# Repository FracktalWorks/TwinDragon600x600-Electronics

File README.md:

# TwinDragon600x600-Electronics
Electronic description, pinout and manuals for the electronics used in Twin Dragon 600x600x600 (Enhanced Size)

### For the Combination of BTT Manta M8P V2.0 + RPi CM4 + RP2040 based toolboard

Pin Configurations, jumper selection, CanBus and multi-MCU wiring to RPi CM4 embedded onto BTT Manta M8P V2.0 for Twin Dragon 600x600x600

Components used:
1. BTT Manta M8P V2.0 - 1
2. RPi CM4 (embed onto BTT Manta M8P V2.0) - 1
3. RP2040 based Can Module/Toolboard - 2
4. TMC5160 Stepper drivers - 4
5. TMC5160T Plus Z driver - 1
6. TMC2209 stepper drivers - 2 (External) + 2 (Present on the Toolboards)
7. BTT HDMI5 Touch Display

## Setting up BTT Manta M8P V2.0 + RPi CM4 + RP2040 based toolboard

After powering on the M8P, the LED on the bottom left corner will light up to indicate normal power supply. The VUSB jumper in the center is for selecting power - it should only be shorted when powering the board via USB or supplying power out via USB.

### Other Initial preparation and setting up jumpers

#### TMC Driver SPI Mode

The first row are the defined pin for the drivers, which are either high or low when shorted or unshorted to establish different mode of communication. The second row are defined with the SPI modes, with the namings of 'MISO', 'CS', 'SCK' and 'MOSI' when read from left to right. Since we use the TMC5160 driver, it specifically operates only on the SPI mode. Insert the jumpers corresponding to its parallel pins only on the 1st and the 2nd row as shown in the image.

#### TMC Driver UART Mode

The given set of pin to short is the CS pin that enables only the uart mode.

#### Driver Voltage selection

For High Voltage selection(48V):

Since the TMC5160 operates only on SPI mode, which is specifically for achieving faster communication and higher speeds, it needs an operating voltage of around 48V. The manta M8P has seperte pins for regular voltage of 24V and high voltage of 48V, that is to be jumped to the common pin of voltage supply to the drivers. We jump the HV pin in the left to the middle pin of supply in order to provide 48V to the drivers, as shown in the image above.

For normal Voltage selection (24V):

This voltage selection can be used when using a regular TMC2209 on the UART mode

#### Setting up jumper for probe activation

The pin for probe used here is the IND-probe pin on Manta M8P V2.0, and the jumpers are placed on the two pins beside the probe pins, and other three perpendicular pins to its right, where the top two are to jumped together to activate the probe pin, as shown in the image above, to enable 24V/5V supply to the ABL board. The three columns of the pins starting from the top are 5V, 12V, 24V Respectively.

#### Setting up Jumper for CANBUS communication

At the left of the CAN pin, a small jumper is to be placed on the pins that mention '120R' depicting the 120 ohms resistance that is applied on the CAN Low and High communication pins. This is a crucial pin for the setting up of the CAN communication of the motherboard and toolboard.

## Wiring and Connections

The overall connections of all the Electrical and Electronic components are present in the image above

### BTT Manta M8P V2.0 Pin connections

## Dragon ToolBoard Pinout Mappings

## Guide to place the connectors on the Carriage Minifit Board

## To setup Raspeberry Pi camera Rev 1.3, interfaced with RPi CM4 and BTT Manta M8P/M5P

In order to interface the Pi camera Rev 1.3 with the RPi CM4 and BTT Manta M8P/M5P, flip the board and check for a CSI1 camera slot, which should look like the image below

Instructions to attach the camera in BTT Manta M8P V2.0

Instructions to attach the camera in BTT Manta M8P V2.0

1. Now, boot up the board (including CM4), SSH into the CM4 and open the terminal
2. We will have to download a bin file into the boot folder of the CM4, below is the command to enter into the terminal.

`sudo wget https://datasheets.raspberrypi.com/cmio/dt-blob-cam1.bin -O /boot/dt-blob.bin`

If the above command does not work, try the following command:

`sudo wget https://datasheets.raspberrypi.com/cmio/dt-blob-cam1.bin -O /boot/firmware/dt-blob.bin`

3. Now, in the terminal, enter `sudo raspi-config` and select the option '3 Interface Options    Configure connections to peripherals'. Now select the first option 'P1 Camera      Enable/disable connection to the Raspberry Pi Camera'. A pop-up would appear where it asks to enable the camera. Make sure to select <yes> and exit the portal.

4. Now, in the terminal, type in `sudo nano /boot/config.txt` and make sure the settings are enabled

   `start_x=1
   gpu_mem=128`

   Note: make sure `#camera_auto_select=1` is commented out, or else it will not work.

For more clarifications, check out 'Julia TouchUI documentation' for more settings on Pi-camera

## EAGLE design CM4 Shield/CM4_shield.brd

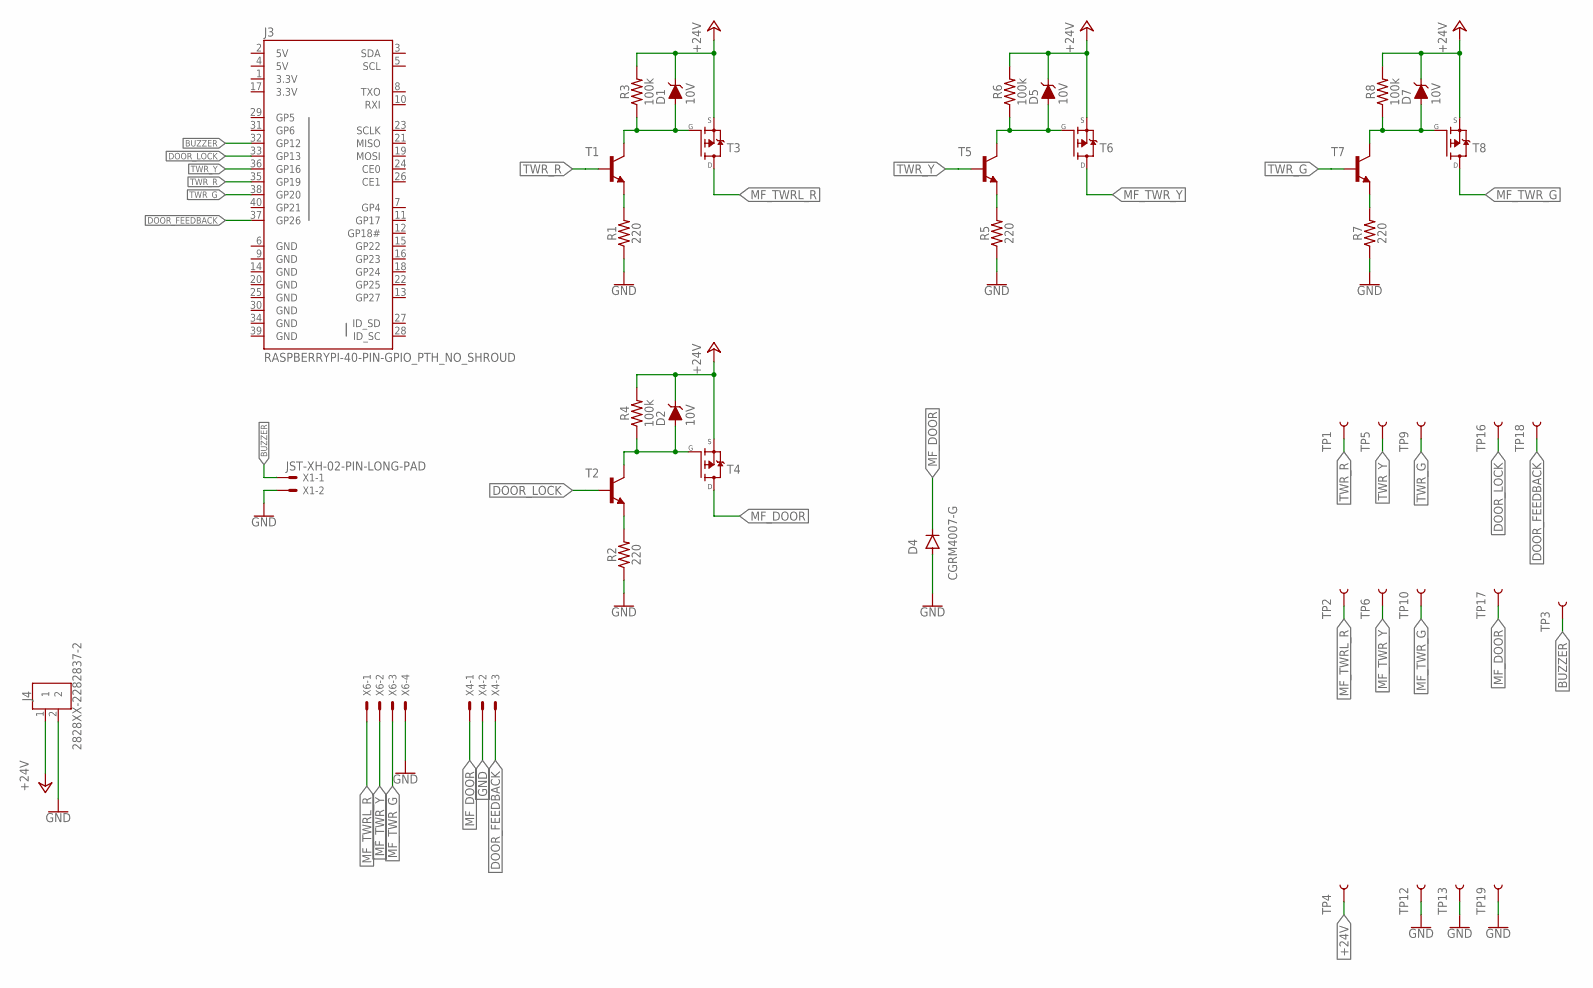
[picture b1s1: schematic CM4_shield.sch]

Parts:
D1, D2, D5, D7: 10V; PANASONIC_SMINI2-F5-B
D4: CGRM4007-G; SOD-123_MINI-SMA
J3: RASPBERRYPI-40-PIN-GPIO_PTH_NO_SHROUD; 2X20
J4: 2828XX-2282837-2; TERMBLK_508-2N
R1, R2, R5, R7: 220; 0603
R3, R4, R6, R8: 100k; 0603
T1, T2, T5, T7: MMBT3904LT1-NPN-SOT23-BEC; SOT23-BEC
T3, T4, T6, T8: MOSFET_P_SOT223; MOSFET_SOT223
TP1, TP2, TP3, TP4, TP5, TP6, TP9, TP10, TP12, TP13, TP16, TP17, TP18, TP19: TEST-POINT3X5; PAD.03X.05
X1: JST-XH-02-PIN-LONG-PAD; JST-XH-02-PACKAGE-LONG-PAD
X4: DOOR LOCK; JST-XH-03-PACKAGE-LONG-PAD
X6: TOWER LIGHT; JST-XH-04-PACKAGE-LONG-PAD

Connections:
3.3V: J3.1 (3.3V), J3.17 (3.3V)
5V: J3.2 (5V), J3.4 (5V)
+24V: D1.C, D2.C, D5.C, D7.C, J4.1, R3.2, R4.2, R6.2, R8.2, T3.3 (S), T4.3 (S), T6.3 (S), T8.3 (S), TP4.P$1
BUZZER: J3.32 (GP12), TP3.P$1, X1.1
DOOR_FEEDBACK: J3.37 (GP26), TP18.P$1, X4.3
DOOR_LOCK: J3.33 (GP13), T2.B, TP16.P$1
GND: D4.A, J3.6 (GND), J3.9 (GND), J3.14 (GND), J3.20 (GND), J3.25 (GND), J3.30 (GND), J3.34 (GND), J3.39 (GND), J4.2, R1.1, R2.1, R5.1, R7.1, TP12.P$1, TP13.P$1, TP19.P$1, X1.2, X4.2, X6.4
MF_DOOR: D4.C, T4.2 (D), T4.4 (D), TP17.P$1, X4.1
MF_TWRL_R: T3.2 (D), T3.4 (D), TP2.P$1, X6.1
MF_TWR_G: T8.2 (D), T8.4 (D), TP10.P$1, X6.3
MF_TWR_Y: T6.2 (D), T6.4 (D), TP6.P$1, X6.2
unnamed: R1.2, T1.E
unnamed: D5.A, R6.1, T5.C, T6.1 (G)
unnamed: D1.A, R3.1, T1.C, T3.1 (G)
unnamed: R5.2, T5.E
unnamed: D7.A, R8.1, T7.C, T8.1 (G)
unnamed: R7.2, T7.E
unnamed: D2.A, R4.1, T2.C, T4.1 (G)
unnamed: R2.2, T2.E
TWR_G: J3.38 (GP20), T7.B, TP9.P$1
TWR_R: J3.35 (GP19), T1.B, TP1.P$1
TWR_Y: J3.36 (GP16), T5.B, TP5.P$1

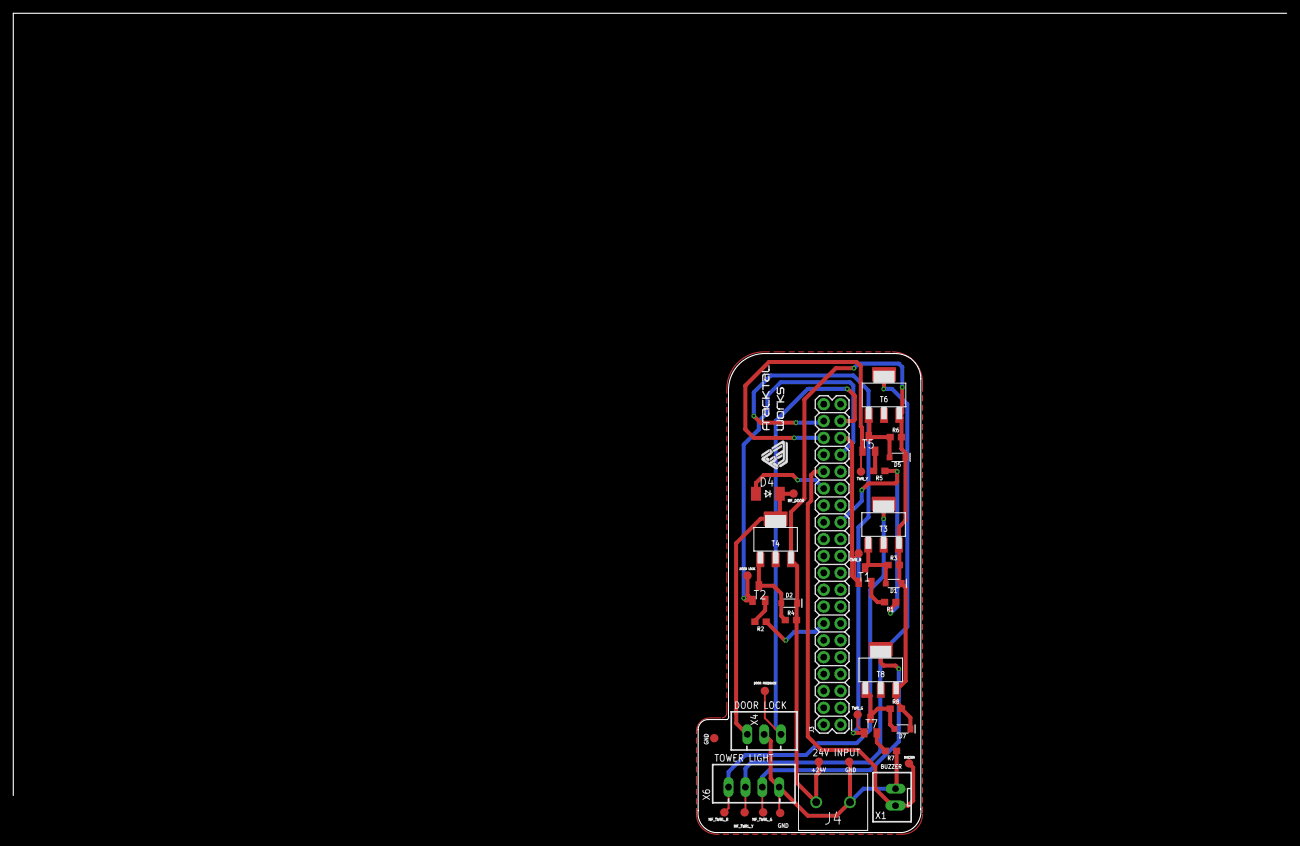
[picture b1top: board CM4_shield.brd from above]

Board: 2 copper layers, 33.6 x 72.1 mm, 41 parts (0 on the bottom side), 22 nets.

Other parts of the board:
U$1: FWLOGO_SMALL

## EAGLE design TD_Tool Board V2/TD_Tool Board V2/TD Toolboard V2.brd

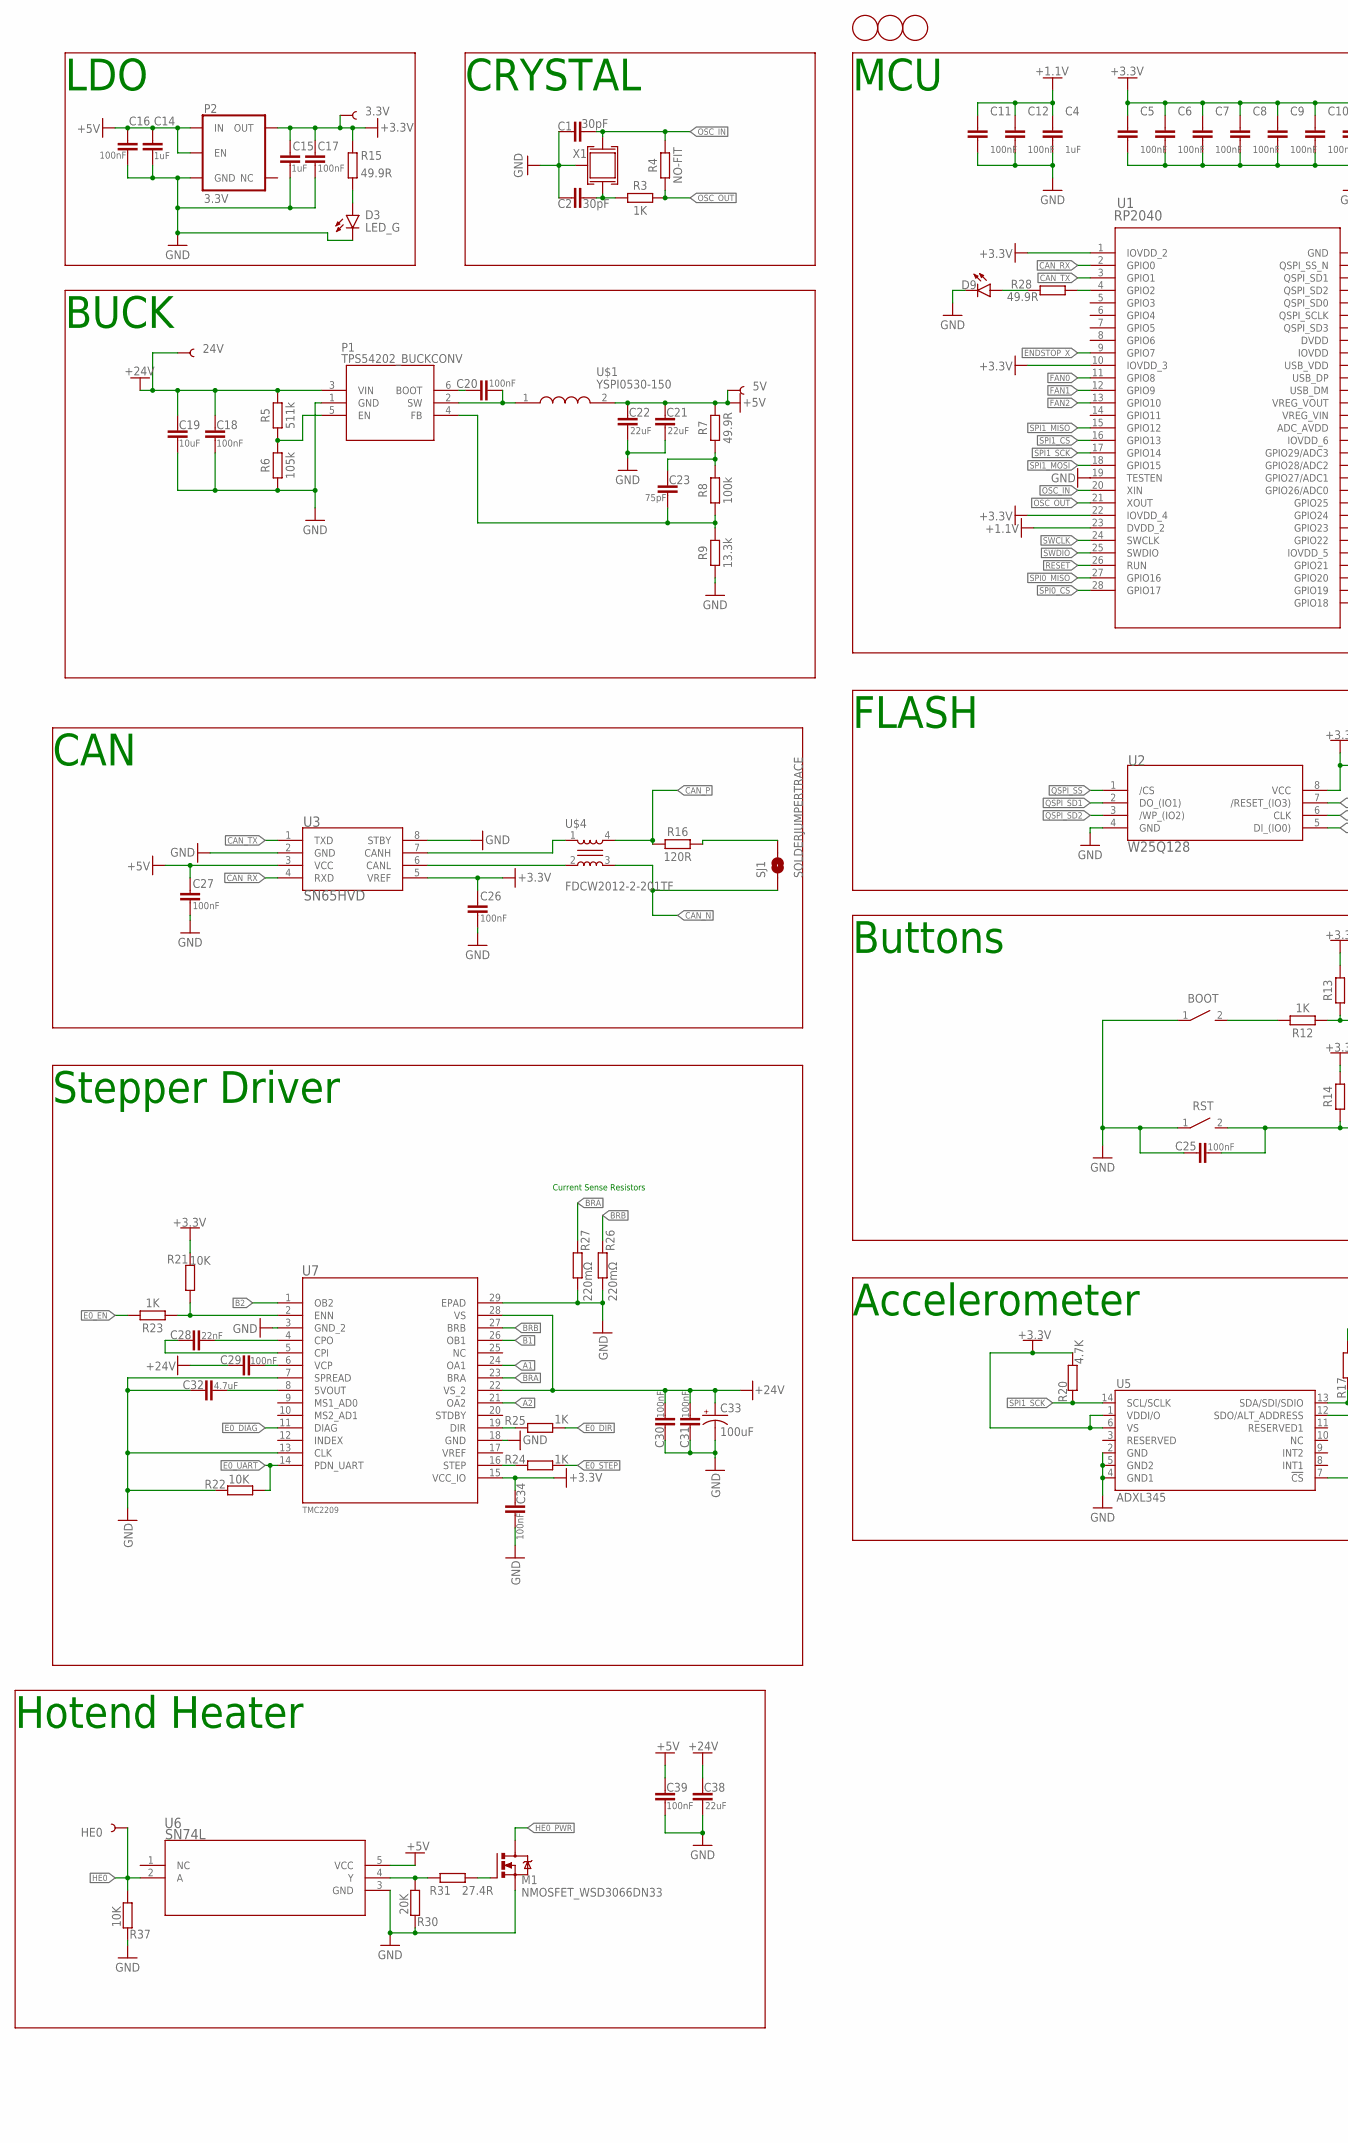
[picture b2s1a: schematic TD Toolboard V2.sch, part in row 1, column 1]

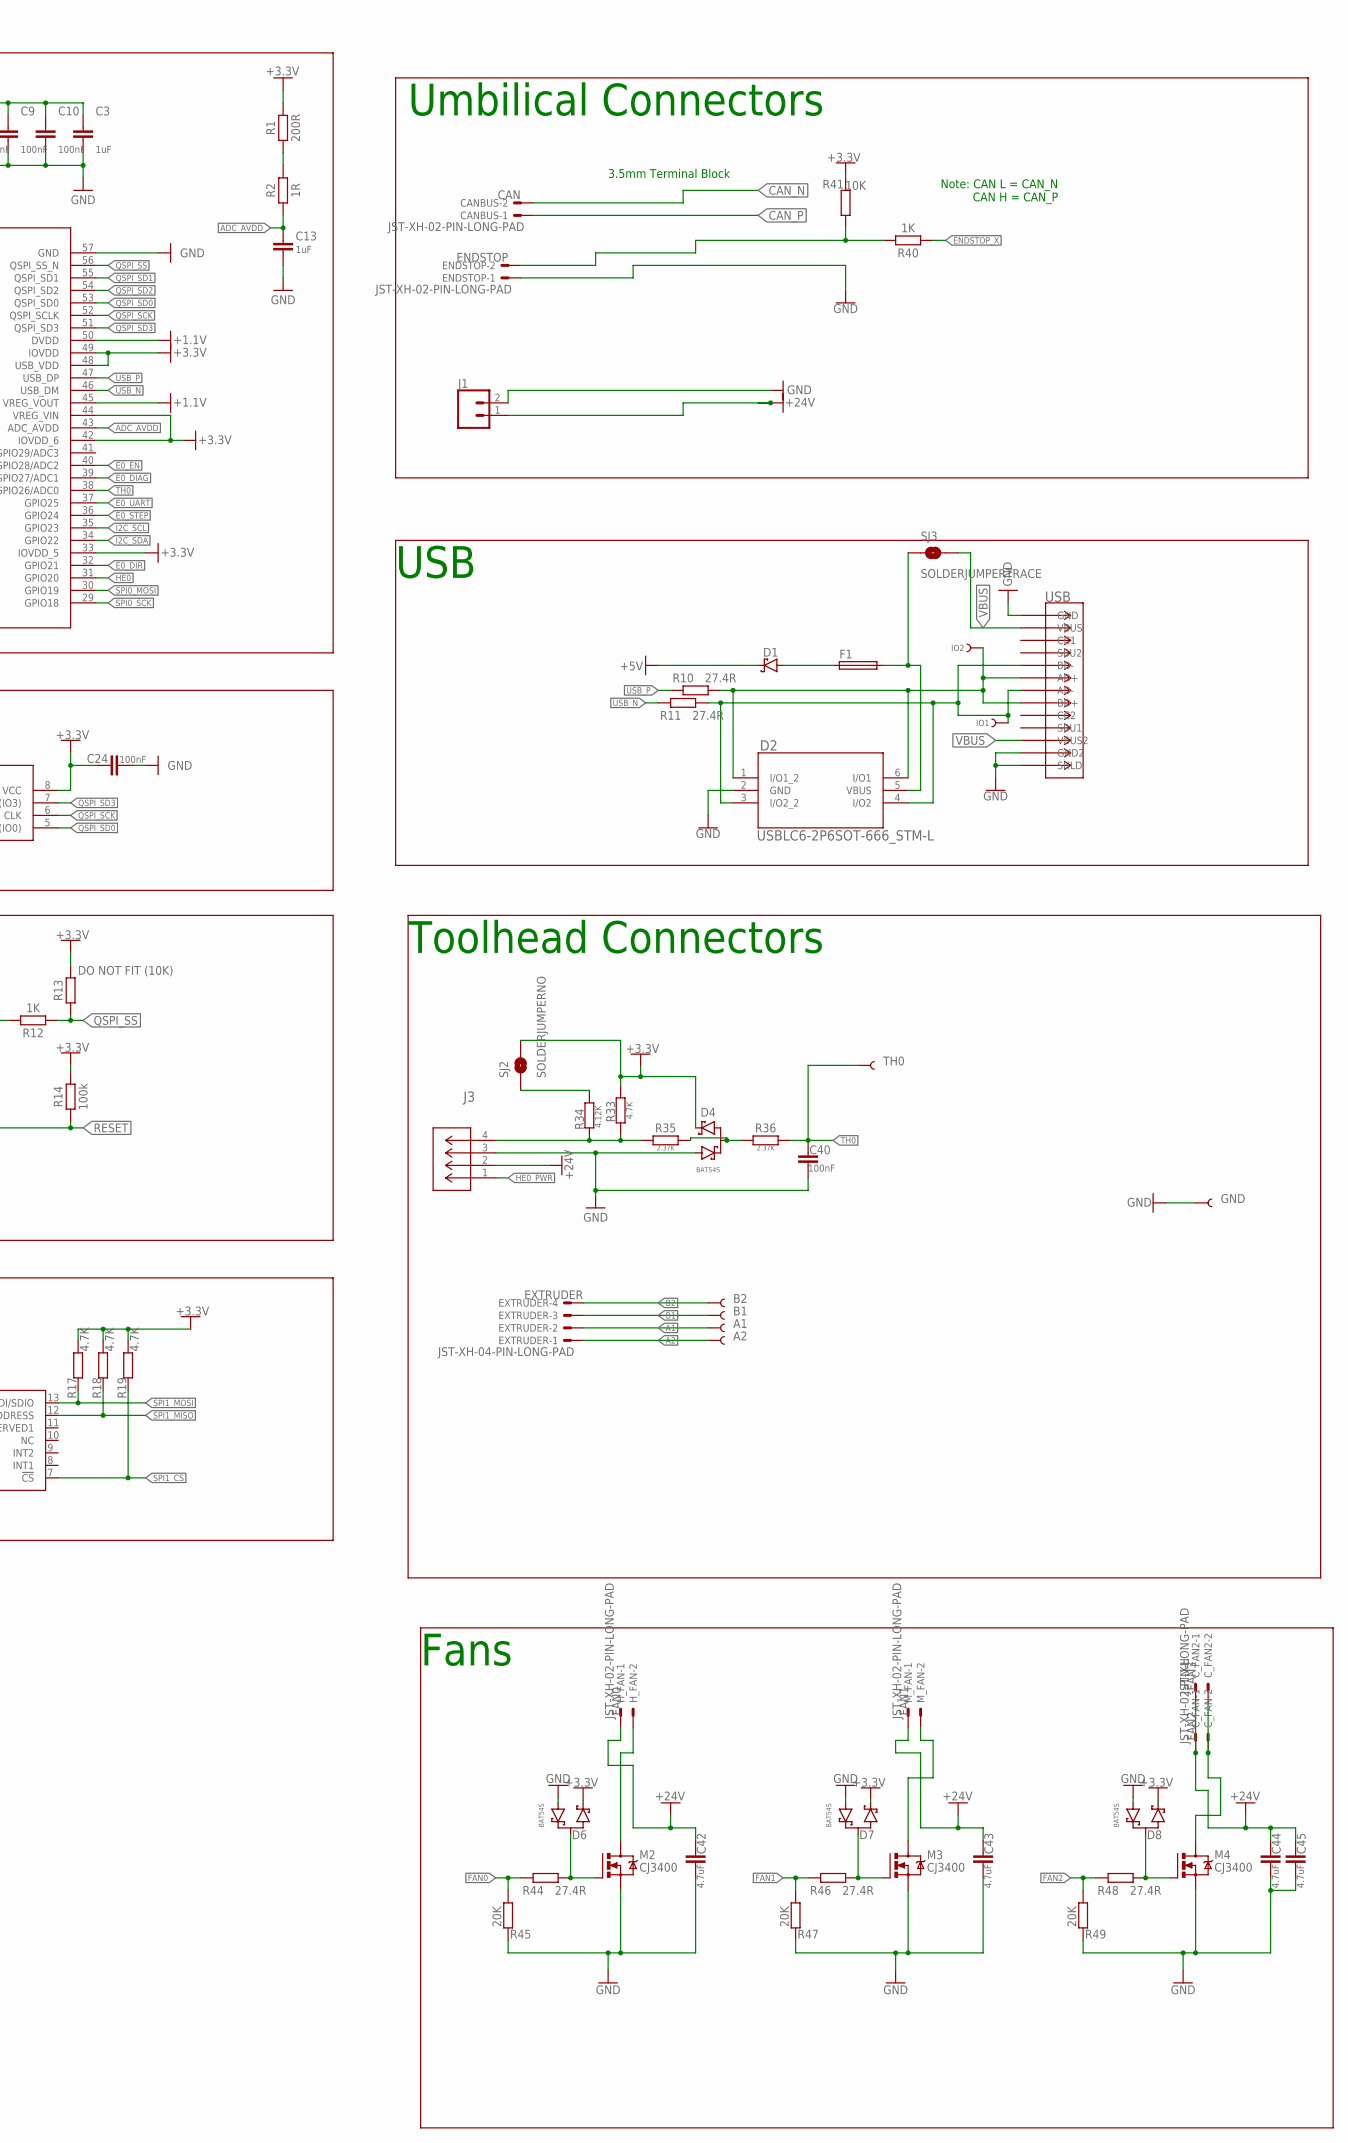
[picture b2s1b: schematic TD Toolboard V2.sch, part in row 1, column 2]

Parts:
3.3V, 5V, 24V: TEST-POINT3X4; PAD.03X.04
A1, A2: TEST-POINT3X4; PAD.03X.04
B1, B2: TEST-POINT3X4; PAD.03X.04
BOOT: B3U-1000P(M)-B; LCSCPN# C231329
C1, C2: 30pF; CAPC1005X60; LCSCPN# C1570
C3, C4, C13, C14, C15: 1uF; CAPC1005X60; LCSCPN# C52923
C5, C6, C7, C8, C9, C10, C11, C12, C16, C17, C18, C20, C24, C25, C26, C27, C29, C30, C31, C34, C39, C40: 100nF; CAPC1005X60; LCSCPN# C307331
C19: 10uF; CAPC1608X85; LCSCPN# C194427
C21, C22, C38: 22uF; CAPC2012X110; LCSCPN# C338080
C23: 75pF; CAPC1005X60; LCSCPN# C37809
C28: 22nF; CAPC1005X60; LCSCPN# C1532
C32, C42, C43, C44, C45: 4.7uF; CAPC1608X85; LCSCPN# C162274
C33: 100uF; PANASONIC_D; LCSCPN# C128464
CANBUS: JST-XH-02-PIN-LONG-PAD; JST-XH-02-PACKAGE-LONG-PAD
C_FAN: JST-XH-02-PIN-LONG-PAD; JST-XH-02-PACKAGE-LONG-PAD
C_FAN2: JST-XH; JST-XH-02-PACKAGE-LONG-PAD
D1: MBR0520LT1G; SODFL3718X115
D2: USBLC6-2P6SOT-666_STM-L; SOT-666_STM-L; LCSCPN# C2827693
D3: LED_G; LEDC1608X35N_FLAT-G; LCSCPN# C72043
D4, D6, D7, D8: BAT54S; SOT23; LCSCPN# C47546
D9: LED_G; LED3MM; LCSCPN# C72043
ENDSTOP: JST-XH-02-PIN-LONG-PAD; JST-XH-02-PACKAGE-LONG-PAD
EXTRUDER: JST-XH-04-PIN-LONG-PAD; JST-XH-04-PACKAGE-LONG-PAD
F1: FUSE_CHIP-0603(1608-METRIC); FUSC1608X60N; LCSCPN# C261937
FD4, FD5, FD6: FIDUCIAL; FIDUCIAL_1MM
GND: TEST-POINT3X4; PAD.03X.04
HE0: TEST-POINT3X4; PAD.03X.04
H_FAN: JST-XH-02-PIN-LONG-PAD; JST-XH-02-PACKAGE-LONG-PAD
IO1, IO2: TEST-POINT3; PAD.03X.03
J1: CONN_023.5MM; SCREWTERMINAL-3.5MM-2
J3: JST-MICROFIT; CON_430450400_MOL
M1: NMOSFET_WSD3066DN33; LCSCPN# C148386
M2, M3, M4: CJ3400; SOT23; LCSCPN# C19019
M_FAN: JST-XH-02-PIN-LONG-PAD; JST-XH-02-PACKAGE-LONG-PAD
P1: TPS54202_BUCKCONV; SOT-23-6; LCSCPN# C191884
P2: 3.3V; SOT23-5; LCSCPN# C51118
R1: 200R; RESC1005X40; LCSCPN# C25087
R2: 1R; RESC1005X40; LCSCPN# C25086
R3, R12, R23, R24, R25, R40: 1K; RESC1005X40; LCSCPN# C25543
R4: NO-FIT; RESC1005X40; LCSCPN# NO-FIT
R5: 511k; RESC1005X40; LCSCPN# C3037035
R6: 105k; RESC1005X40; LCSCPN# C2933067
R7, R15, R28: 49.9R; RESC1005X40; LCSCPN# C25120
R8, R14: 100k; RESC1005X40; LCSCPN# C25741
R9: 13.3k; RESC1005X40; LCSCPN# C2974007
R10, R11, R31, R44, R46, R48: 27.4R; RESC1005X40; LCSCPN# C31439
R13: DO NOT FIT (10K); RESC1005X40; LCSCPN# NO-FIT
R16: 120R; RESC1005X40; LCSCPN# C25079
R17, R18, R19, R20, R33: 4.7K; RESC1005X40; LCSCPN# C304616
R21, R22, R37, R41: 10K; RESC1005X40; LCSCPN# C25744
R26, R27: 220mΩ; RESC1005X40; LCSCPN# C705474
R30, R45, R47, R49: 20K; RESC1005X40; LCSCPN# C25765
R34: 4.12K; RESC1005X40; LCSCPN# C227106
R35, R36: 2.37K; RESC1005X40; LCSCPN# C425373
RST: B3U-1000P(M)-B; LCSCPN# C231329
SJ1, SJ3: SOLDERJUMPERTRACE; SJ_2S-TRACE
SJ2: SOLDERJUMPERNO; SJ_2S-NO
TH0: TEST-POINT3X4; PAD.03X.04
U1: RP2040; IC57_RP2040-L; LCSCPN# C2040
U2: W25Q128; SOIC_128JVSIQ_WIN-L; LCSCPN# C97521
U3: SN65HVD; D8-L; LCSCPN# C14019
U5: ADXL345; ADXL345_LGA14; LCSCPN# C9667
U6: SN74L; DBV5-L; LCSCPN# C7836
U7: TMC2209; QFN28_5X5_3X8_EPAD_TRI; LCSCPN# C2150710
U$1: YSPI0530-150
U$4: FDCW2012-2-201TF
USB: USB-C(KH-TYPE-C-16P); CONN12_KH-TYPE-C-16P; LCSCPN# C709357
X1: CRYSTAL_TAXM12M4RLBDDT2T_3225; CRYSTAL_3225; LCSCPN# C133334

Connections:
+1.1V: C4.1, C11.1, C12.1, U1.23 (DVDD_2), U1.45 (VREG_VOUT), U1.50 (DVDD)
+3.3V: 3.3V.P$1, C3.1, C5.1, C6.1, C7.1, C8.1, C9.1, C10.1, C15.1, C17.1, C24.1, C26.1, C34.1, D4.2, D6.2, D7.2, D8.2, P2.5 (OUT), R1.2, R13.2, R14.2, R15.2, R17.2, R18.2, R19.2, R20.2, R21.1, R33.2, R41.1, SJ2.2, U1.1 (IOVDD_2), U1.10 (IOVDD_3), U1.22 (IOVDD_4), U1.33 (IOVDD_5), U1.42 (IOVDD_6), U1.44 (VREG_VIN), U1.48 (USB_VDD), U1.49 (IOVDD), U2.8 (VCC), U3.5 (VREF), U5.1 (VDDI/O), U5.6 (VS), U7.15 (VCC_IO)
+5V: 5V.P$1, C14.1, C16.1, C21.1, C22.1, C27.1, C39.1, D1.1 (C), P2.1 (IN), P2.3 (EN), R7.2, U3.3 (VCC), U6.5 (VCC), U$1.2
+24V: 24V.P$1, C18.1, C19.1, C29.1, C30.2, C31.2, C33.+, C38.1, C42.1, C43.1, C44.1, C45.1, C_FAN.1, C_FAN2.1, H_FAN.1, J1.1, J3.2, M_FAN.1, P1.3 (VIN), R5.2, U7.22 (VS_2), U7.28 (VS)
A1: A1.P$1, EXTRUDER.2, U7.24 (OA1)
A2: A2.P$1, EXTRUDER.1, U7.21 (OA2)
ADC_AVDD: C13.1, R2.1, U1.43 (ADC_AVDD)
ADC_R: R1.1, R2.2
B1: B1.P$1, EXTRUDER.3, U7.26 (OB1)
B2: B2.P$1, EXTRUDER.4, U7.1 (OB2)
BCBOOT: C20.1, P1.6 (BOOT)
BRA: R27.2, U7.23 (BRA)
BRB: R26.2, U7.27 (BRB)
CAN1_N: U3.6 (CANL), U$4.2
CAN1_P: U3.7 (CANH), U$4.1
CAN_N: CANBUS.2, SJ1.1, U$4.3
CAN_P: CANBUS.1, R16.1, U$4.4
CAN_RX: U1.2 (GPIO0), U3.4 (RXD)
CAN_TX: U1.3 (GPIO1), U3.1 (TXD)
CNT: R16.2, SJ1.2
DIR: R25.2, U7.19 (DIR)
E0_DIAG: U1.39 (GPIO27/ADC1), U7.11 (DIAG)
E0_DIR: R25.1, U1.32 (GPIO21)
E0_EN: R23.2, U1.40 (GPIO28/ADC2)
E0_STEP: R24.1, U1.36 (GPIO24)
E0_UART: R22.2, U1.37 (GPIO25), U7.14 (PDN_UART)
ENDSTOP_X: R40.1, U1.9 (GPIO7)
EX: ENDSTOP.2, R40.2, R41.2
FAN0: R44.2, R45.2, U1.11 (GPIO8)
FAN0G: D6.3, M2.1 (G), R44.1
FAN1: R46.2, R47.2, U1.12 (GPIO9)
FAN1G: D7.3, M3.1 (G), R46.1
FAN2: R48.2, R49.2, U1.13 (GPIO10)
FAN2G: D8.3, M4.1 (G), R48.1
GND: BOOT.1, C1.2, C2.1, C3.2, C4.2, C5.2, C6.2, C7.2, C8.2, C9.2, C10.2, C11.2, C12.2, C13.2, C14.2, C15.2, C16.2, C17.2, C18.2, C19.2, C21.2, C22.2, C24.2, C25.1, C26.2, C27.2, C30.1, C31.1, C32.1, C33.-, C34.2, C38.2, C39.2, C40.2, C42.2, C43.2, C44.2, C45.2, D2.2 (GND), D3.C, D4.1, D6.1, D7.1, D8.1, D9.K (C), ENDSTOP.1, GND.P$1, J1.2, J3.3, M1.P$1 (S), M1.P$2 (S), M1.P$3 (S), M2.2 (S), M3.2 (S), M4.2 (S), P1.1 (GND), P2.2 (GND), R6.1, R9.1, R22.1, R26.1, R27.1, R30.1, R37.1, R45.1, R47.1, R49.1, RST.1, U1.19 (TESTEN), U1.57 (GND), U2.4 (GND), U3.2 (GND), U3.8 (STBY), U5.2 (GND), U5.4 (GND1), U5.5 (GND2), U6.3 (GND), U7.3 (GND_2), U7.7 (SPREAD), U7.13 (CLK), U7.18 (GND), U7.29 (EPAD), USB.1 (GND), USB.12 (GND2), USB.13 (SHLD), USB.14 (SHLD), USB.15 (SHLD), USB.16 (SHLD), USB.18 (SHLD), USB.19 (SHLD), USB.20 (SHLD), USB.21 (SHLD), USB.24 (SHLD), USB.25 (SHLD), USB.26 (SHLD), USB.27 (SHLD), USB.28 (SHLD), USB.29 (SHLD), USB.37 (SHLD), USB.39 (SHLD), USB.41 (SHLD), USB.43 (SHLD), X1.P$2 (GND), X1.P$4 (GND)
GPIOLED: D9.A, R28.1
HE0: HE0.P$1, R37.2, U1.31 (GPIO20), U6.2 (A)
HE0A: R30.2, R31.2, U6.4 (Y)
HE0B: M1.P$4 (G), R31.1
HE0_PWR: J3.1, M1.P$5 (D), M1.P$6 (D), M1.P$7 (D), M1.P$8 (D), M1.P$9 (D)
I2C_SCL: U1.35 (GPIO23)
I2C_SDA: U1.34 (GPIO22)
LDOLED: D3.A, R15.1
LED: R28.2, U1.4 (GPIO2)
unnamed: H_FAN.2, M2.3 (D)
unnamed: M3.3 (D), M_FAN.2
unnamed: C_FAN.2, C_FAN2.2, M4.3 (D)
OSC_IN: C1.1, R4.2, U1.20 (XIN), X1.P$1 (P1)
OSC_OUT: R3.2, R4.1, U1.21 (XOUT)
QSPI_SCK: U1.52 (QSPI_SCLK), U2.6 (CLK)
QSPI_SD0: U1.53 (QSPI_SD0), U2.5 (DI_(IO0))
QSPI_SD1: U1.55 (QSPI_SD1), U2.2 (DO_(IO1))
QSPI_SD2: U1.54 (QSPI_SD2), U2.3 (/WP_(IO2))
QSPI_SD3: U1.51 (QSPI_SD3), U2.7 (/RESET_(IO3))
QSPI_SS: R12.1, R13.1, U1.56 (QSPI_SS_N), U2.1 (/CS)
RESET: C25.2, R14.1, RST.2, U1.26 (RUN)
SPI0_CS: U1.28 (GPIO17)
SPI0_MISO: U1.27 (GPIO16)
SPI0_MOSI: U1.30 (GPIO19)
SPI0_SCK: U1.29 (GPIO18)
SPI1_CS: R19.1, U1.16 (GPIO13), U5.7 (!CS)
SPI1_MISO: R18.1, U1.15 (GPIO12), U5.12 (SDO/ALT_ADDRESS)
SPI1_MOSI: R17.1, U1.18 (GPIO15), U5.13 (SDA/SDI/SDIO)
SPI1_SCK: R20.1, U1.17 (GPIO14), U5.14 (SCL/SCLK)
STEP: R24.2, U7.16 (STEP)
SWB: BOOT.2, R12.2
SWCLK: U1.24 (SWCLK)
SWDIO: U1.25 (SWDIO)
TH0: C40.1, R36.2, TH0.P$1, U1.38 (GPIO26/ADC0)
TH0A: J3.4, R33.1, R34.1, R35.1
TH0B: D4.3, R35.2, R36.1
TH0C: R34.2, SJ2.1
TMC5V: C32.2, U7.8 (5VOUT)
TMCCPI: C28.1, U7.5 (CPI)
TMCCPO: C28.2, U7.4 (CPO)
TMCENN: R21.2, R23.1, U7.2 (ENN)
TMCVCP: C29.2, U7.6 (VCP)
USB1_N: D2.3 (I/O2_2), D2.4 (I/O2), IO1.P$1, R11.1, USB.5 (BD-), USB.7 (AD-)
USB1_P: D2.1 (I/O1_2), D2.6 (I/O1), IO2.P$1, R10.1, USB.6 (AD+), USB.8 (BD+)
USB_N: R11.2, U1.46 (USB_DM)
USB_P: R10.2, U1.47 (USB_DP)
VBUS: SJ3.2, USB.2 (VBUS), USB.11 (VBUS2)
VBUS1: D2.5 (VBUS), F1.2, SJ3.1
VBUS3: D1.2 (A), F1.1
VRC: C23.1, R7.1, R8.2
VREGEN: P1.5 (EN), R5.1, R6.2
VREGFB: C23.2, P1.4 (FB), R8.1, R9.2
VREGO: C20.2, P1.2 (SW), U$1.1
XR: C2.2, R3.1, X1.P$3 (P2)

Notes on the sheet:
LDO
BUCK
CRYSTAL
MCU
FLASH
Buttons
Accelerometer
CAN
Stepper Driver
Current Sense Resistors
Hotend Heater
Umbilical Connectors
Note: CAN L = CAN_N CAN H = CAN_P
3.5mm Terminal Block
USB
Toolhead Connectors
Fans

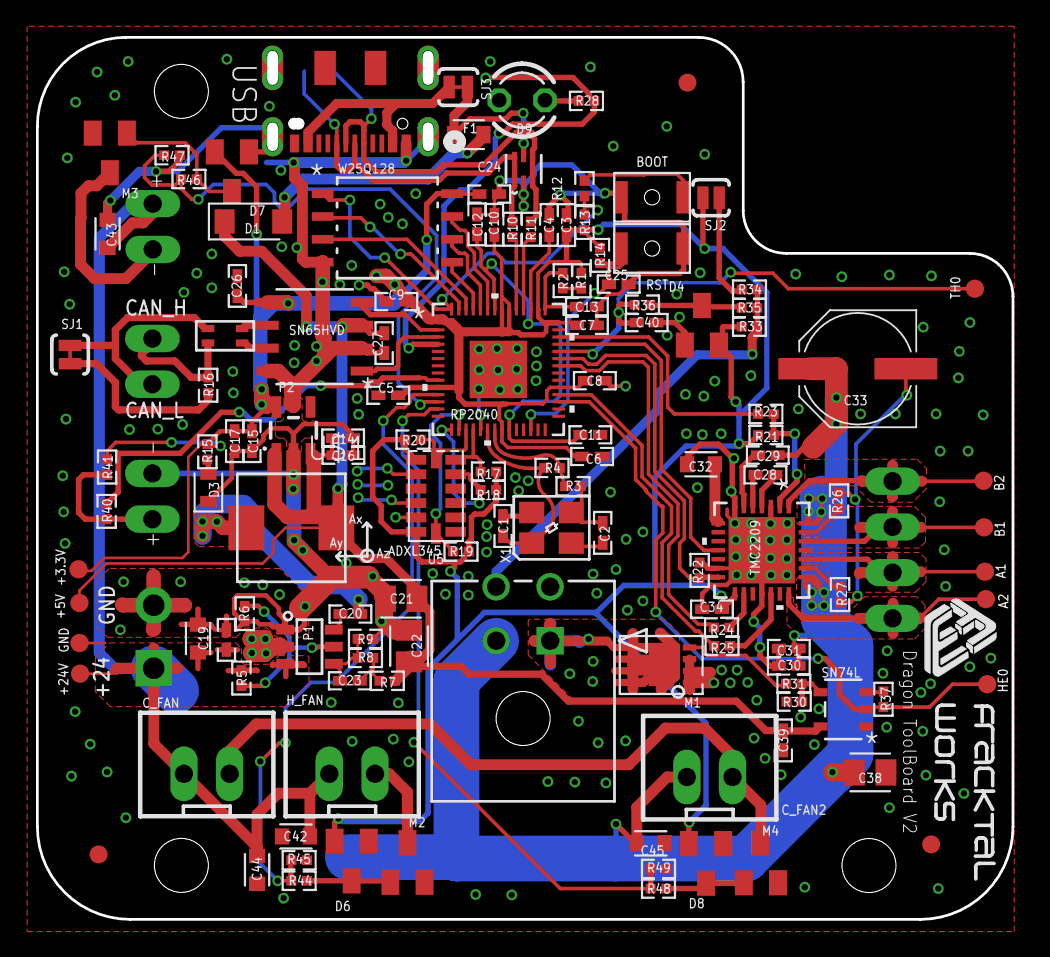
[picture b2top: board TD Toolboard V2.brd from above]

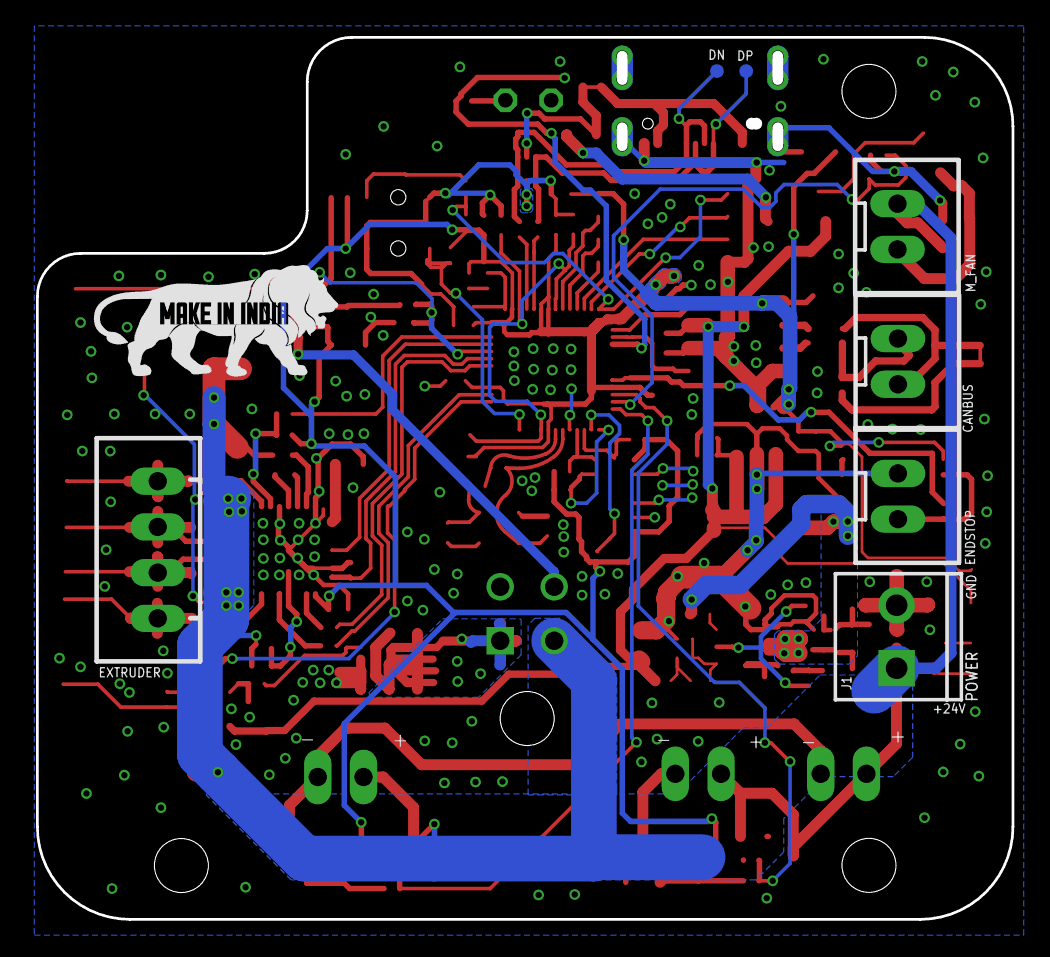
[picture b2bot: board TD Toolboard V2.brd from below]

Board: 2 copper layers, 54.2 x 49.0 mm, 140 parts (8 on the bottom side), 81 nets.

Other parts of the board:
U$2: MAKEININDIA
U$3: FWLOGO_SMALL

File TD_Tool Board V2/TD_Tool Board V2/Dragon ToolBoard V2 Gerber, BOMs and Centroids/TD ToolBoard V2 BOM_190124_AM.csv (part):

Qty,Designator,Footprint,Comment,LCSC Part#,Description,Value,Device,Package,Parts,Description,BUILT_BY,CAN,CATEGORY,COLOR,COPYRIGHT,CURRENT_RATING,DATASHEET,DESCRIPTION,DIGI-KEY_PART_NUMBER_1,DIGI-KEY_PART_NUMBER_2,DIGI-KEY_PART_NUMBER_3,DIGI-KEY_PART_NUMBER_4,DRAIN_CURRENT,ENDSTOP,EXTRUDER,FAN0,FAN1,FAN2,FAN3,FORWARD_CURRENT,LCSCPN#,MANUFACTURER,MANUFACTURER_PART_NUMBER,MFR_NAME,MPN,OPERATING_TEMP,OPERATING_TEMPERATURE,PART_STATUS,POPULARITY,PROD_ID,RATING,REVERSE_VOLTAGE,ROHS_COMPLIANCE,ROHS_COMPLIANT,SERIES,SOURCELIBRARY,SUB-CATEGORY,SUBCATEGORY,THERMALLOSS,THERMAL_LOSS,TOLERANCE,TYPE,VALUE,VENDOR,VOLTAGE_RATING,ZENER_VOLTAGE
1,J1,SCREWTERMINAL-3.5MM-2,CONN_023.5MM,,Multi connection point. Often used as Generic Header-pin footprint for 0.1 inch spaced/style header connections,,CONN_023.5MM,SCREWTERMINAL-3.5MM-2,J1,Multi connection point. Often used as Generic Header-pin footprint for 0.1 inch spaced/style header connections,,,,,,,,,,,,,,,,,,,,,,,,,,,,,,CONN-08399,,,,,,,,,,,,,,,,
2,"R8, R14",RESC1005X40,R_CHIP-0402(1005-METRIC),C25741,Resistor Fixed - Generic,100k,R_CHIP-0402(1005-METRIC),RESC1005X40,"R8, R14",Resistor Fixed - Generic,,,Resistor,,,,,,,,,,,,,,,,,,C25741,,,,,,,,,,,,,,,,Fixed,,,,,,,,,
22,"C5, C6, C7, C8, C9, C10, C11, C12, C16, C17, C18, C20, C24, C25, C26, C27, C29, C30, C31, C34, C39, C40",CAPC1005X60,C_CHIP-0402(1005-METRIC),C307331,Capacitor - Generic,100nF,C_CHIP-0402(1005-METRIC),CAPC1005X60,"C5, C6, C7, C8, C9, C10, C11, C12, C16, C17, C18, C20, C24, C25, C26, C27, C29, C30, C31, C34, C39, C40",Capacitor - Generic,,,Capacitor,,,,,,,,,,,,,,,,,,C307331,,,,,,,,,,,,,,,,,,,,,,,,,
1,C33,PANASONIC_D,100UF-POLAR-25V-20%(ELEC),C128464,100µF polarized capacitors,100uF,100UF-POLAR-25V-20%(ELEC),PANASONIC_D,C33,100µF polarized capacitors,,,,,,,,,,,,,,,,,,,,,C128464,,,,,,,,,CAP-12547,,,,,,,,,,,,,100uF,,,
1,R6,RESC1005X40,R_CHIP-0402(1005-METRIC),C2933067,Resistor Fixed - Generic,105k,R_CHIP-0402(1005-METRIC),RESC1005X40,R6,Resistor Fixed - Generic,,,Resistor,,,,,,,,,,,,,,,,,,C2933067,,,,,,,,,,,,,,,,Fixed,,,,,,,,,
4,"R21, R22, R37, R41",RESC1005X40,R_CHIP-0402(1005-METRIC),C25744,Resistor Fixed - Generic,10K,R_CHIP-0402(1005-METRIC),RESC1005X40,"R21, R22, R37, R41",Resistor Fixed - Generic,,,Resistor,,,,,,,,,,,,,,,,,,C25744,,,,,,,,,,,,,,,,Fixed,,,,,,,,,
1,C19,CAPC1608X85,C_CHIP-0603(1608-METRIC),C194427,Capacitor - Generic,10uF,C_CHIP-0603(1608-METRIC),CAPC1608X85,C19,Capacitor - Generic,,,Capacitor,,,,,,,,,,,,,,,,,,C194427,,,,,,,,,,,,,,,,,,,,,,,,,
1,R16,RESC1005X40,R_CHIP-0402(1005-METRIC),C25079,Resistor Fixed - Generic,120R,R_CHIP-0402(1005-METRIC),RESC1005X40,R16,Resistor Fixed - Generic,,,Resistor,,,,,,,,,,,,,,,,,,C25079,,,,,,,,,,,,,,,,Fixed,,,,,,,,,
1,R9,RESC1005X40,R_CHIP-0402(1005-METRIC),C2974007,Resistor Fixed - Generic,13.3k,R_CHIP-0402(1005-METRIC),RESC1005X40,R9,Resistor Fixed - Generic,,,Resistor,,,,,,,,,,,,,,,,,,C2974007,,,,,,,,,,,,,,,,Fixed,,,,,,,,,
6,"R3, R12, R23, R24, R25, R40",RESC1005X40,R_CHIP-0402(1005-METRIC),C25543,Resistor Fixed - Generic,1K,R_CHIP-0402(1005-METRIC),RESC1005X40,"R3, R12, R23, R24, R25, R40",Resistor Fixed - Generic,,,Resistor,,,,,,,,,,,,,,,,,,C25543,,,,,,,,,,,,,,,,Fixed,,,,,,,,,
1,R2,RESC1005X40,R_CHIP-0402(1005-METRIC),C25086,Resistor Fixed - Generic,1R,R_CHIP-0402(1005-METRIC),RESC1005X40,R2,Resistor Fixed - Generic,,,Resistor,,,,,,,,,,,,,,,,,,C25086,,,,,,,,,,,,,,,,Fixed,,,,,,,,,
5,"C3, C4, C13, C14, C15",CAPC1005X60,C_CHIP-0402(1005-METRIC),C52923,Capacitor - Generic,1uF,C_CHIP-0402(1005-METRIC),CAPC1005X60,"C3, C4, C13, C14, C15",Capacitor - Generic,,,Capacitor,,,,,,,,,,,,,,,,,,C52923,,,,,,,,,,,,,,,,,,,,,,,,,
2,"R35, R36",RESC1005X40,R_CHIP-0402(1005-METRIC),C425373,Resistor Fixed - Generic,2.37K,R_CHIP-0402(1005-METRIC),RESC1005X40,"R35, R36",Resistor Fixed - Generic,,,Resistor,,,,,,,,,,,,,,,,,,C425373,,,,,,,,,,,,,,,,Fixed,,,,,,,,,
1,R1,RESC1005X40,R_CHIP-0402(1005-METRIC),C25087,Resistor Fixed - Generic,200R,R_CHIP-0402(1005-METRIC),RESC1005X40,R1,Resistor Fixed - Generic,,,Resistor,,,,,,,,,,,,,,,,,,C25087,,,,,,,,,,,,,,,,Fixed,,,,,,,,,
4,"R30, R45, R47, R49",RESC1005X40,R_CHIP-0402(1005-METRIC),C25765,Resistor Fixed - Generic,20K,R_CHIP-0402(1005-METRIC),RESC1005X40,"R30, R45, R47, R49",Resistor Fixed - Generic,,,Resistor,,,,,,,,,,,,,,,,,,C25765,,,,,,,,,,,,,,,,Fixed,,,,,,,,,
2,"R26, R27",RESC1005X40,R_CHIP-0402(1005-METRIC),C705474,Resistor Fixed - Generic,220mΩ,R_CHIP-0402(1005-METRIC),RESC1005X40,"R26, R27",Resistor Fixed - Generic,,,Resistor,,,,,,,,,,,,,,,,,,C705474,,,,,,,,,,,,,,,,Fixed,,,,,,,,,
1,C28,CAPC1005X60,C_CHIP-0402(1005-METRIC),C1532,Capacitor - Generic,22nF,C_CHIP-0402(1005-METRIC),CAPC1005X60,C28,Capacitor - Generic,,,Capacitor,,,,,,,,,,,,,,,,,,C1532,,,,,,,,,,,,,,,,,,,,,,,,,
3,"C21, C22, C38",CAPC2012X110,C_CHIP-0805(2012-METRIC),C338080,Capacitor - Generic,22uF,C_CHIP-0805(2012-METRIC),CAPC2012X110,"C21, C22, C38",Capacitor - Generic,,,Capacitor,,,,,,,,,,,,,,,,,,C338080,,,,,,,,,,,,,,,,,,,,,,,,,
6,"R10, R11, R31, R44, R46, R48",RESC1005X40,R_CHIP-0402(1005-METRIC),C31439,Resistor Fixed - Generic,27.4R,R_CHIP-0402(1005-METRIC),RESC1005X40,"R10, R11, R31, R44, R46, R48",Resistor Fixed - Generic,,,Resistor,,,,,,,,,,,,,,,,,,C31439,,,,,,,,,,,,,,,,Fixed,,,,,,,,,
1,P2,SOT23-5,V_REG_AP2112K-3.3V,C51118,AP2112 - 600mA CMOS LDO Regulator w/ Enable,3.3V,V_REG_AP2112K-3.3V,SOT23-5,P2,AP2112 - 600mA CMOS LDO Regulator w/ Enable,,,,,,,,,,,,,,,,,,,,,C51118,,,,,,,,,VREG-12457,,,,,,,,,,,,,3.3V,,,
2,"C1, C2",CAPC1005X60,C_CHIP-0402(1005-METRIC),C1570,Capacitor - Generic,30pF,C_CHIP-0402(1005-METRIC),CAPC1005X60,"C1, C2",Capacitor - Generic,,,Capacitor,,,,,,,,,,,,,,,,,,C1570,,,,,,,,,,,,,,,,,,,,,,,,,
1,R34,RESC1005X40,R_CHIP-0402(1005-METRIC),C227106,Resistor Fixed - Generic,4.12K,R_CHIP-0402(1005-METRIC),RESC1005X40,R34,Resistor Fixed - Generic,,,Resistor,,,,,,,,,,,,,,,,,,C227106,,,,,,,,,,,,,,,,Fixed,,,,,,,,,
5,"R17, R18, R19, R20, R33",RESC1005X40,R_CHIP-0402(1005-METRIC),C304616,Resistor Fixed - Generic,4.7K,R_CHIP-0402(1005-METRIC),RESC1005X40,"R17, R18, R19, R20, R33",Resistor Fixed - Generic,,,Resistor,,,,,,,,,,,,,,,,,,C304616,,,,,,,,,,,,,,,,Fixed,,,,,,,,,
5,"C32, C42, C43, C44, C45",CAPC1608X85,C_CHIP-0603(1608-METRIC),C162274,Capacitor - Generic,4.7uF,C_CHIP-0603(1608-METRIC),CAPC1608X85,"C32, C42, C43, C44, C45",Capacitor - Generic,,,Capacitor,,,,,,,,,,,,,,,,,,C162274,,,,,,,,,,,,,,,,,,,,,,,,,
3,"R7, R15, R28",RESC1005X40,R_CHIP-0402(1005-METRIC),C25120,Resistor Fixed - Generic,49.9R,R_CHIP-0402(1005-METRIC),RESC1005X40,"R7, R15, R28",Resistor Fixed - Generic,,,Resistor,,,,,,,,,,,,,,,,,,C25120,,,,,,,,,,,,,,,,Fixed,,,,,,,,,
1,R5,RESC1005X40,R_CHIP-0402(1005-METRIC),C3015918,Resistor Fixed - Generic,511k,R_CHIP-0402(1005-METRIC),RESC1005X40,R5,Resistor Fixed - Generic,,,Resistor,,,,,,,,,,,,,,,,,,C3037035,,,,,,,,,,,,,,,,Fixed,,,,,,,,,
1,C23,CAPC1005X60,C_CHIP-0402(1005-METRIC),C37809,Capacitor - Generic,75pF,C_CHIP-0402(1005-METRIC),CAPC1005X60,C23,Capacitor - Generic,,,Capacitor,,,,,,,,,,,,,,,,,,C37809,,,,,,,,,,,,,,,,,,,,,,,,,
1,U5,ADXL345_LGA14,ADXL345BCCZ-RL,C9667,Digital Accelerometer,ADXL345,ADXL345BCCZ-RL,ADXL345_LGA14,U5,Digital Accelerometer,,,SENSOR,,,,,Digital Accelerometer ,,,,,,,,,,,,,C9667,ANALOG DEVICES,,,ADXL345BCCZ-RL,,−55°C to +105°C,ACTIVE,,,,,,RoHS Compliant,ADXL345,,Accelerometer,,,,,3-Axis Digital MEMS Accelerometer,,,,
2,"BOOT, RST",B3U-1000P(M)-B,B3U-X000B3U-1000P(M)-B1000P(M)-B,C231329,Ultra-small Tactile Switch,B3U-1000P(M)-B,B3U-X000B3U-1000P(M)-B1000P(M)-B,B3U-1000P(M)-B,"BOOT, RST",Ultra-small Tactile Switch,,,SWITCH,,,,,Ultra-small Surface-mounting Tactile Switches with High Contact Reliability ,,,,,,,,,,,,,C231329,OMRON,,,,,-25°C to +70°C at 60%RH max,ACTIVE,,,,,,,B3U,,,,,,,Tactile,B3U-1000P(M)-B,,,
4,"D4, D6, D7, D8",SOT23,BAT54S,C47546,,BAT54S,BAT54S,SOT23,"D4, D6, D7, D8",,,,,,,,,,,,,,,,,,,,,,C47546,,,,,,,,,,,,,,,,,,,,,,,,,
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

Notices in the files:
parts and their libraries:
SparkFun-DiscreteSemi: Licensing: Creative Commons ShareAlike 4.0 International - https://creativecommons.org/licenses/by-sa/4.0
COPYRIGHT: Copyright (C) 2023 Ultra Librarian. All rights reserved.
Fracktal Misc Lib: COPYRIGHT: Copyright (C) 2018 Accelerated Designs. All rights reserved
